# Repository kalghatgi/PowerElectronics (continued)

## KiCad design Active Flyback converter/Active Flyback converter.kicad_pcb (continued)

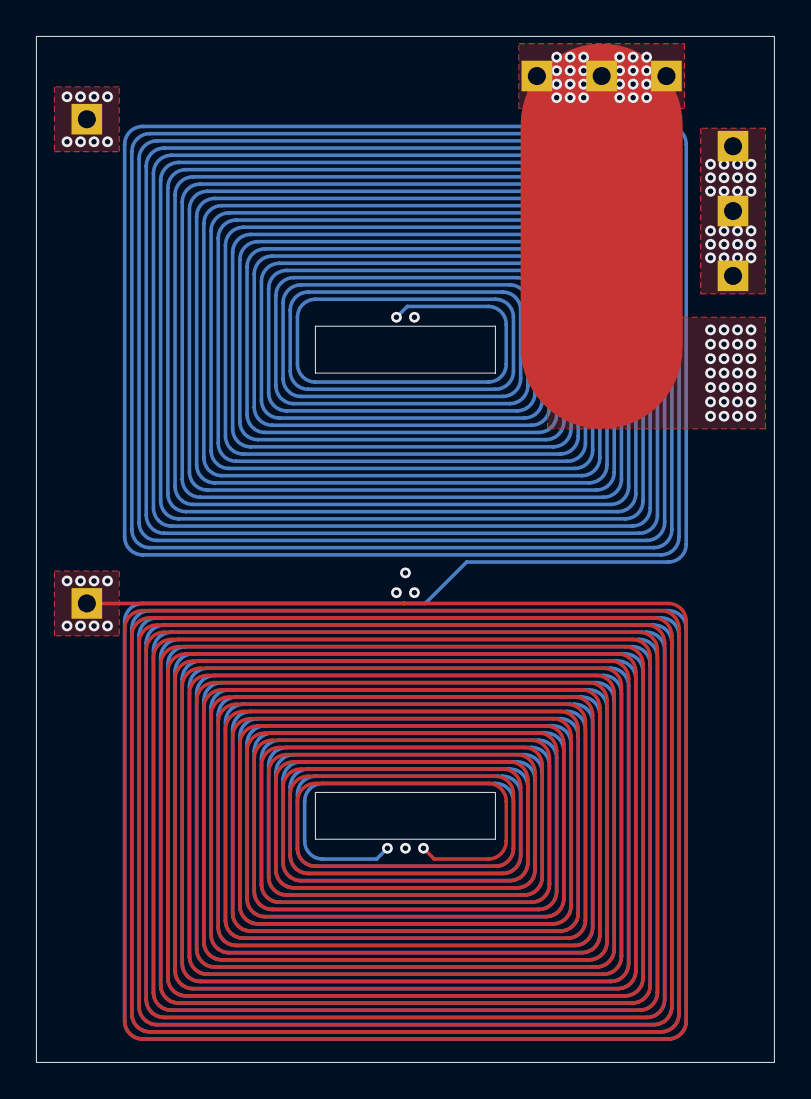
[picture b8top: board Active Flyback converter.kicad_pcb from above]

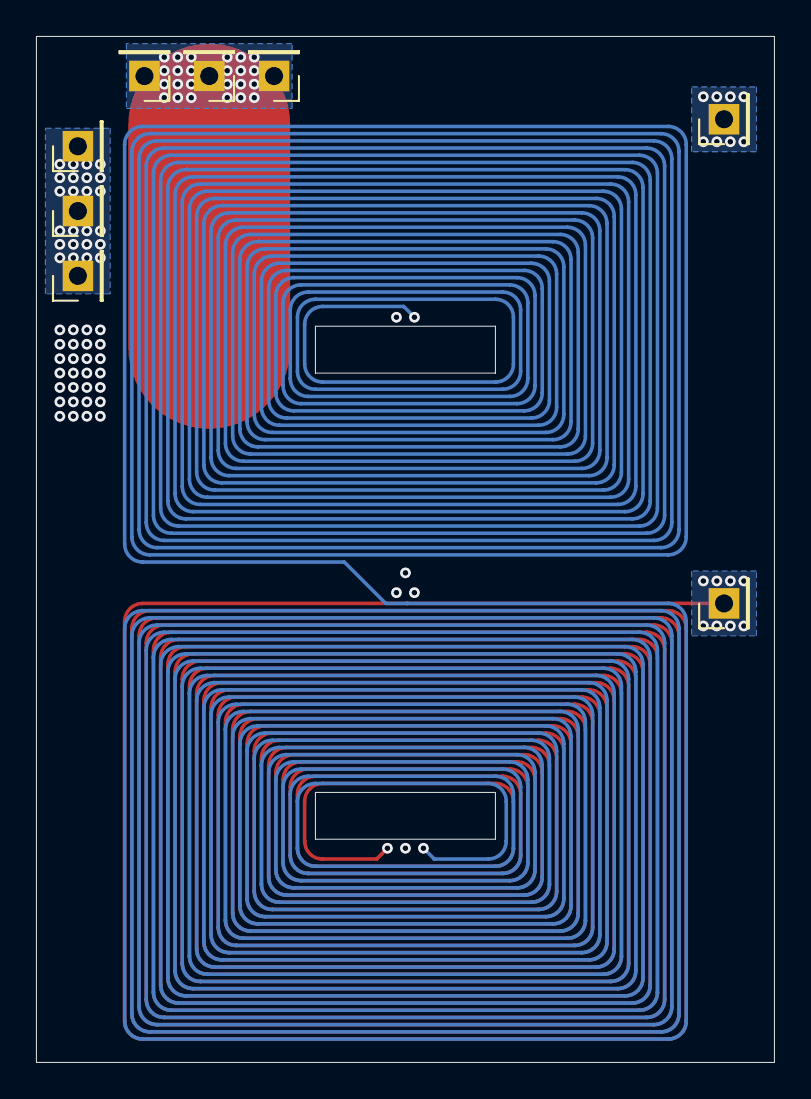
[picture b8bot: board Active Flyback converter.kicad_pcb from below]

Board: 6 copper layers, 41.0 x 57.0 mm, 8 parts (8 on the bottom side), 2 nets.

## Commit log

2024-07-25 Fly-buck converter/LM5160 - v1.0
2024-07-25 Flyback converter/DC-DC step down - v1.0
2024-09-26 Backlink to CADLAB.io has been added.
2024-10-04 3-phase AC-DC off-board charger - v1.0
2025-06-22 Active flyback converter - v1.0
2025-06-28 Active flyback converter - v1.1
2025-09-21 2phase AC-DC charger variant1 and control board v1.0
2025-09-21 Active flyback converter - v1.2
2025-09-21 HV inverter - v1.0
2025-09-21 Active flyback converter (actual v1.2)
2025-10-31 Buck-boost - v1.0
2025-10-31 Dual active bridge - v1.0
2025-10-31 80V_150Ac_250Ap - v1.0
2026-02-24 buck-boost/control & buck-boost/variant1 - corrected the pin-config
2026-02-24 buck-boost/variant2 (full bridge) - v1.0
